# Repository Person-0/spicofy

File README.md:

# **Spicofy v1.0**

A spotify controller with features including play, pause and volume control and an OLED Panel to show the currently playing song along with RGB indicators for status.
> Note: Requires Spotify premium as the Web API does not allow changes to playback state without premium!

<br>

Made as a submission to [hackclub's blueprint](https://blueprint.hackclub.com) with immense help from the [make-your-own-hackpad guide.](https://blueprint.hackclub.com/hackpad)

> *This is my first hardware project! Thank you hackclub for this amazing opportunity!! <3*

[View CAD Files](./v1/CAD/)<br>
[View PCB Files](./v1/PCB/)

## Components Used (BOM)
- Seeed XIAO RP2040 (1x)
- EC11 Rotary encoder (1x)
- MX-Style switches (4x)
- SSD1306 0.91 inch OLED display (1x)
- SK6812 MINI-E LEDs (2x)

## Firmware

### [*Click here to view Firmware files*](./v1/firmware/)
> Host & MCU specific READMEs are available in their respective folders.

- #### MCU:
    - Drives a 0.91' 128x32 OLED Display using the [SSD1306 driver](https://github.com/adafruit/Adafruit_CircuitPython_DisplayIO_SSD1306) that displays the current playback state.
    - Uses [kmk firmware](https://github.com/KMKfw/kmk_firmware) to detect keypress and rotary encoder events.
    - Listens to data from the serial port for current playback state.
    - Sends data to the serial port for changes in the playback state (play/pause, next, volume etc.)
- #### Host (PC connected via USB-C):
    Responsible for getting the access token from the [Spotify Web API](https://developer.spotify.com/documentation/web-api) and relaying information between the API and the MCU.

## Pictures
> Taken from [Fusion 360](https://www.autodesk.com/products/fusion-360/overview) & [KiCad](https://www.kicad.org/)

> Model Credits (grabcad.com)
> - [cherry-mx-switches](https://grabcad.com/library/cherry-mx-switches-mx-1)
> - [seeed-studio-xiao-rp2040](https://grabcad.com/library/seeed-studio-xiao-rp2040-2)
> - [SSD1306-oled-display](https://grabcad.com/library/display-oled128x32-1)
> - [rotary-encoder](https://grabcad.com/library/rotary-encoder-17)
> - [sk6812mini-e-led](https://grabcad.com/library/sk6812mini-e-led-1)

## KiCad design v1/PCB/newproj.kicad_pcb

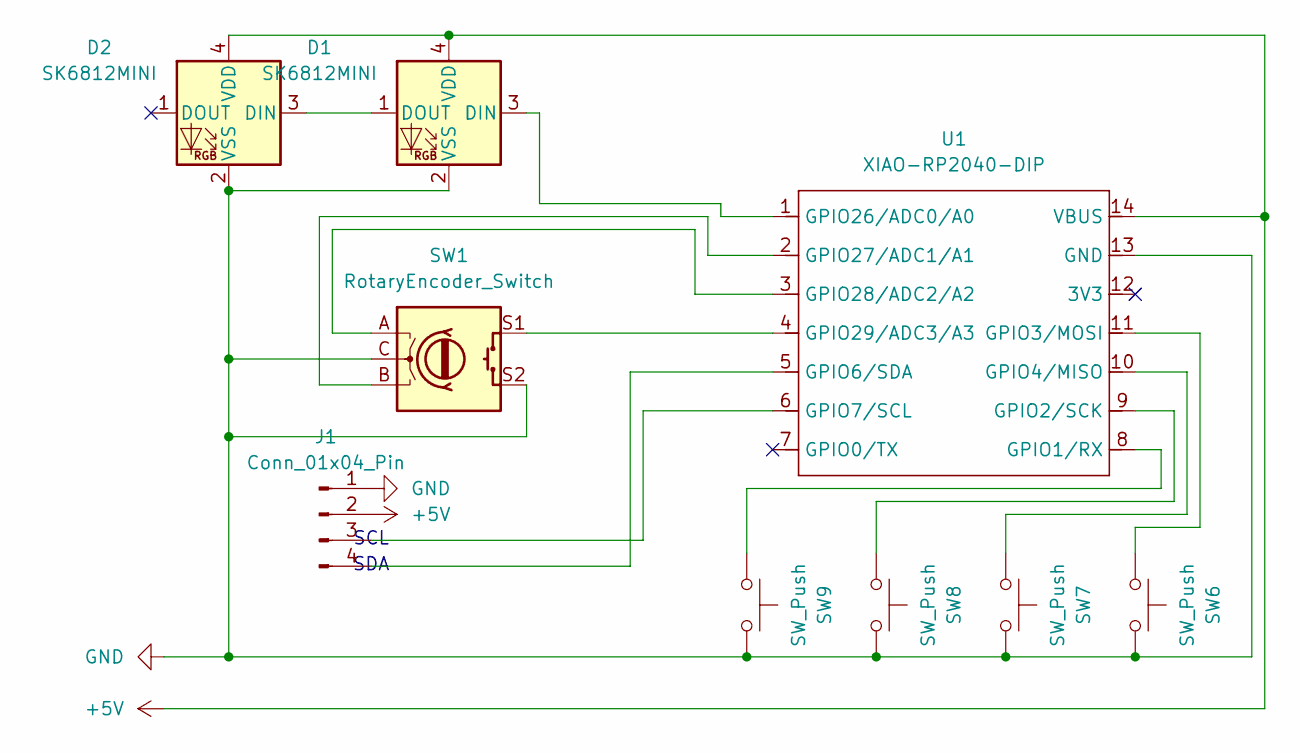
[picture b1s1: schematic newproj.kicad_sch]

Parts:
D1, D2: SK6812MINI; LED_SK6812MINI_PLCC4_3.5x3.5mm_P1.75mm
J1: Conn_01x04_Pin; SSD1306-0.91-OLED-4pin-128x32
SW1: RotaryEncoder_Switch; RotaryEncoder_Alps_EC11E-Switch_Vertical_H20mm
SW6, SW7, SW8, SW9: SW_Push; SW_Cherry_MX_1.00u_PCB
U1: XIAO-RP2040-DIP

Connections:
+5V: D1.4 (VDD), D2.4 (VDD), J1.2, U1.14 (VBUS)
GND: D1.2 (VSS), D2.2 (VSS), J1.1, SW1.C, SW1.S2, SW6.2, SW7.2, SW8.2, SW9.2, U1.13 (GND)
unnamed: D1.3 (DIN), U1.1 (GPIO26/ADC0/A0)
unnamed: D1.1 (DOUT), D2.3 (DIN)
unnamed: J1.3, U1.6 (GPIO7/SCL)
unnamed: J1.4, U1.5 (GPIO6/SDA)
unnamed: SW9.1, U1.8 (GPIO1/RX)
unnamed: SW8.1, U1.9 (GPIO2/SCK)
unnamed: SW6.1, U1.11 (GPIO3/MOSI)
unnamed: SW7.1, U1.10 (GPIO4/MISO)
unnamed: SW1.B, U1.2 (GPIO27/ADC1/A1)
unnamed: SW1.A, U1.3 (GPIO28/ADC2/A2)
unnamed: SW1.S1, U1.4 (GPIO29/ADC3/A3)

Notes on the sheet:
SDA
SCL

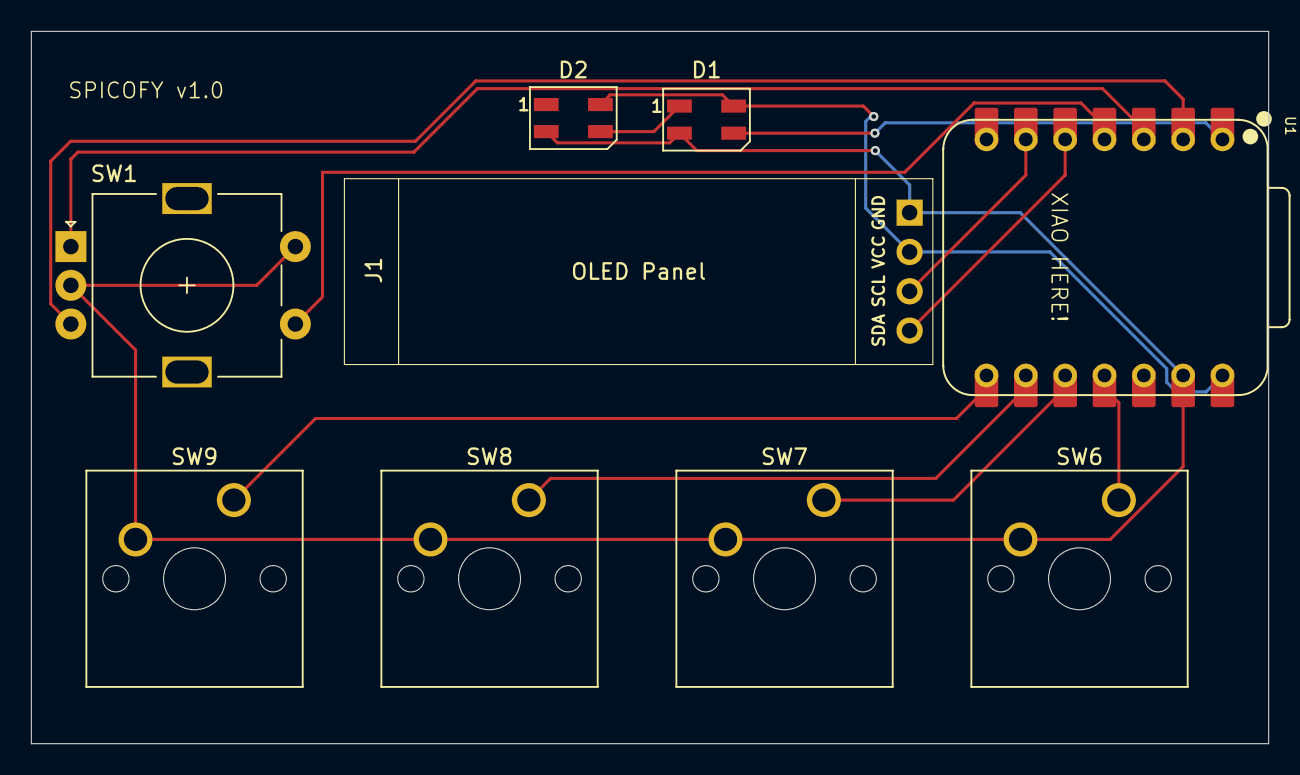
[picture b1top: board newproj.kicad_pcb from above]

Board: 2 copper layers, 79.9 x 46.0 mm, 9 parts (0 on the bottom side), 13 nets.

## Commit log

2025-12-28 directory restructuring, minor updates, fixes for circuit
2025-12-28 add note
2025-12-29 update firmware info
2025-12-29 re-structure directory
2025-12-29 begin host service part of the firmware
2025-12-29 exclude built files from git
2025-12-29 use pnpm to save storage :D
2025-12-29 implemented serial port selection logic
2025-12-29 indent using tabs cuz vscode decided to use spaces for some reason
2025-12-29 tabs
2025-12-29 spotify auth flow
2025-12-29 typo fix
2025-12-30 added getCurrenState method
2025-12-30 bit by bit controls logic
2025-12-30 updated controls
2025-12-30 minor formatting changes
2025-12-30 removed test stuff from host firmware
2025-12-30 update state after track ends
2025-12-30 added more info to state packet
2025-12-30 update state edgecase
2025-12-30 begin data processing
2025-12-30 stop express app after receiving spotify oath code
2025-12-30 added readme for MCU part
2025-12-30 update ssd1306 driver link, format code a bit
2025-12-30 updated oled to show status
2025-12-30 code structuring, minor bugfix
2025-12-30 fix zero division error, parse message only if not None
2025-12-30 add readme for host firmware stuff
2025-12-30 better readme
2025-12-30 added cad & pcb files
2026-01-01 fix broken link
